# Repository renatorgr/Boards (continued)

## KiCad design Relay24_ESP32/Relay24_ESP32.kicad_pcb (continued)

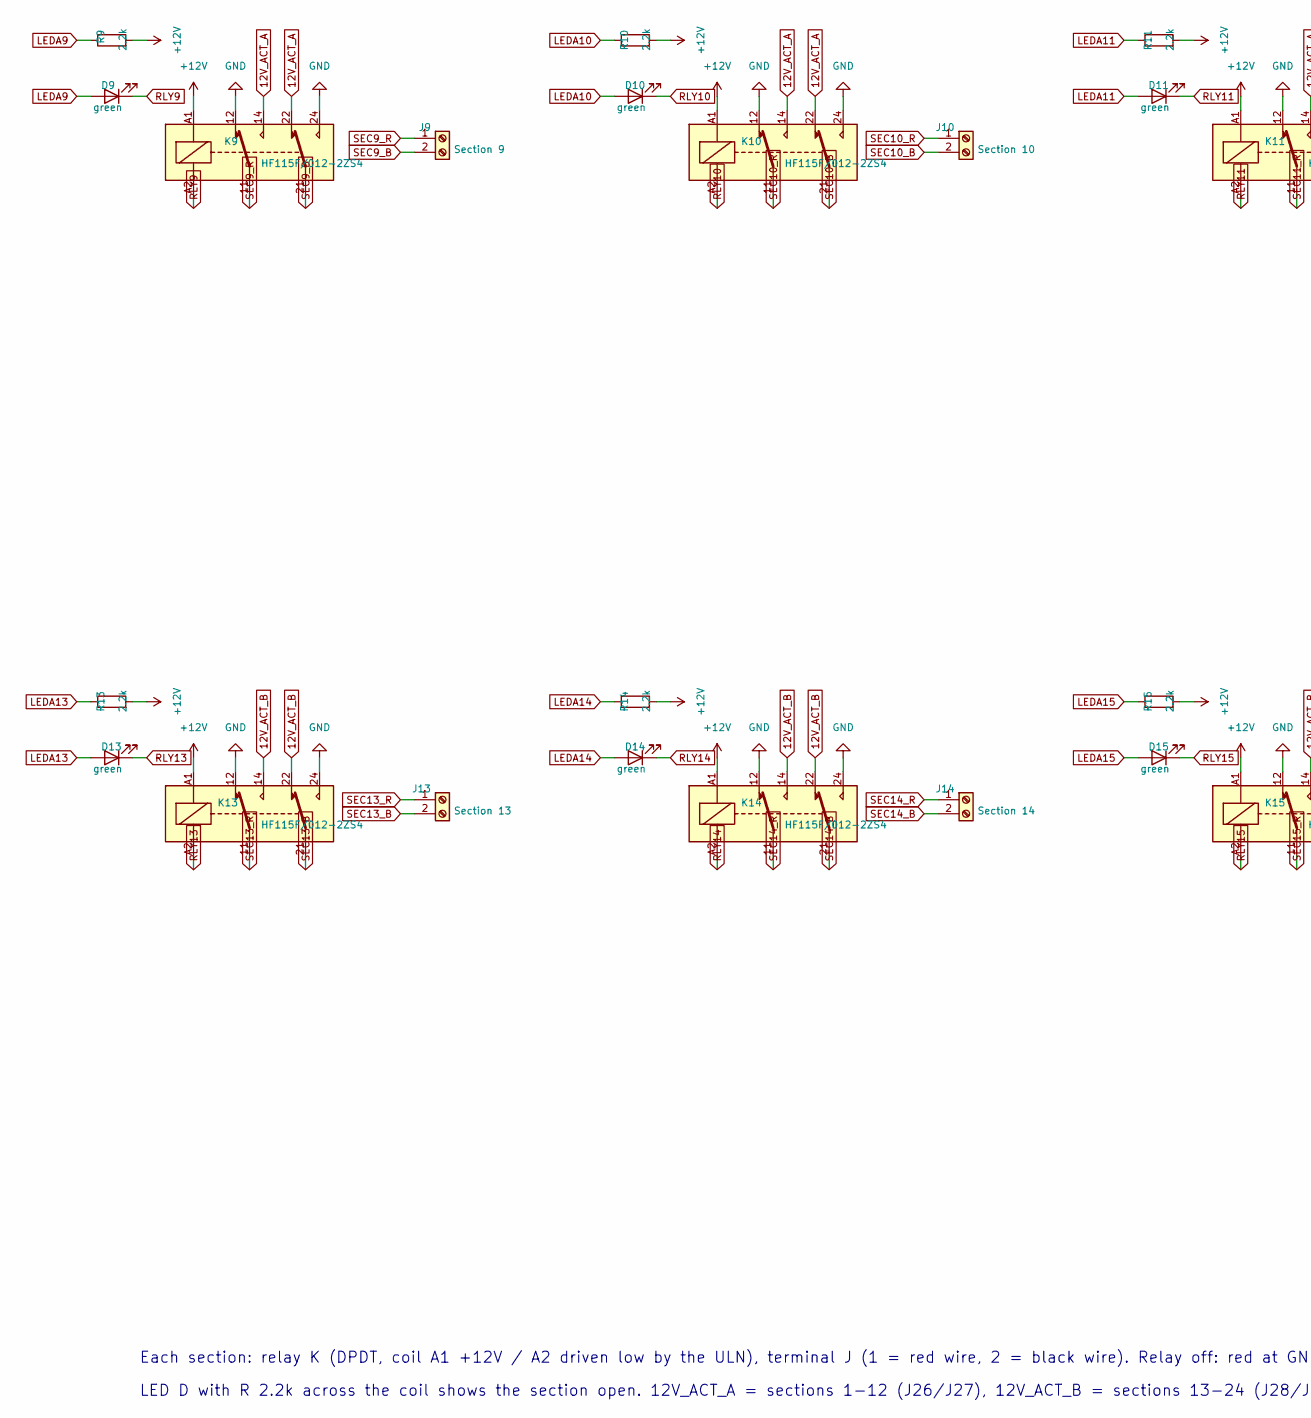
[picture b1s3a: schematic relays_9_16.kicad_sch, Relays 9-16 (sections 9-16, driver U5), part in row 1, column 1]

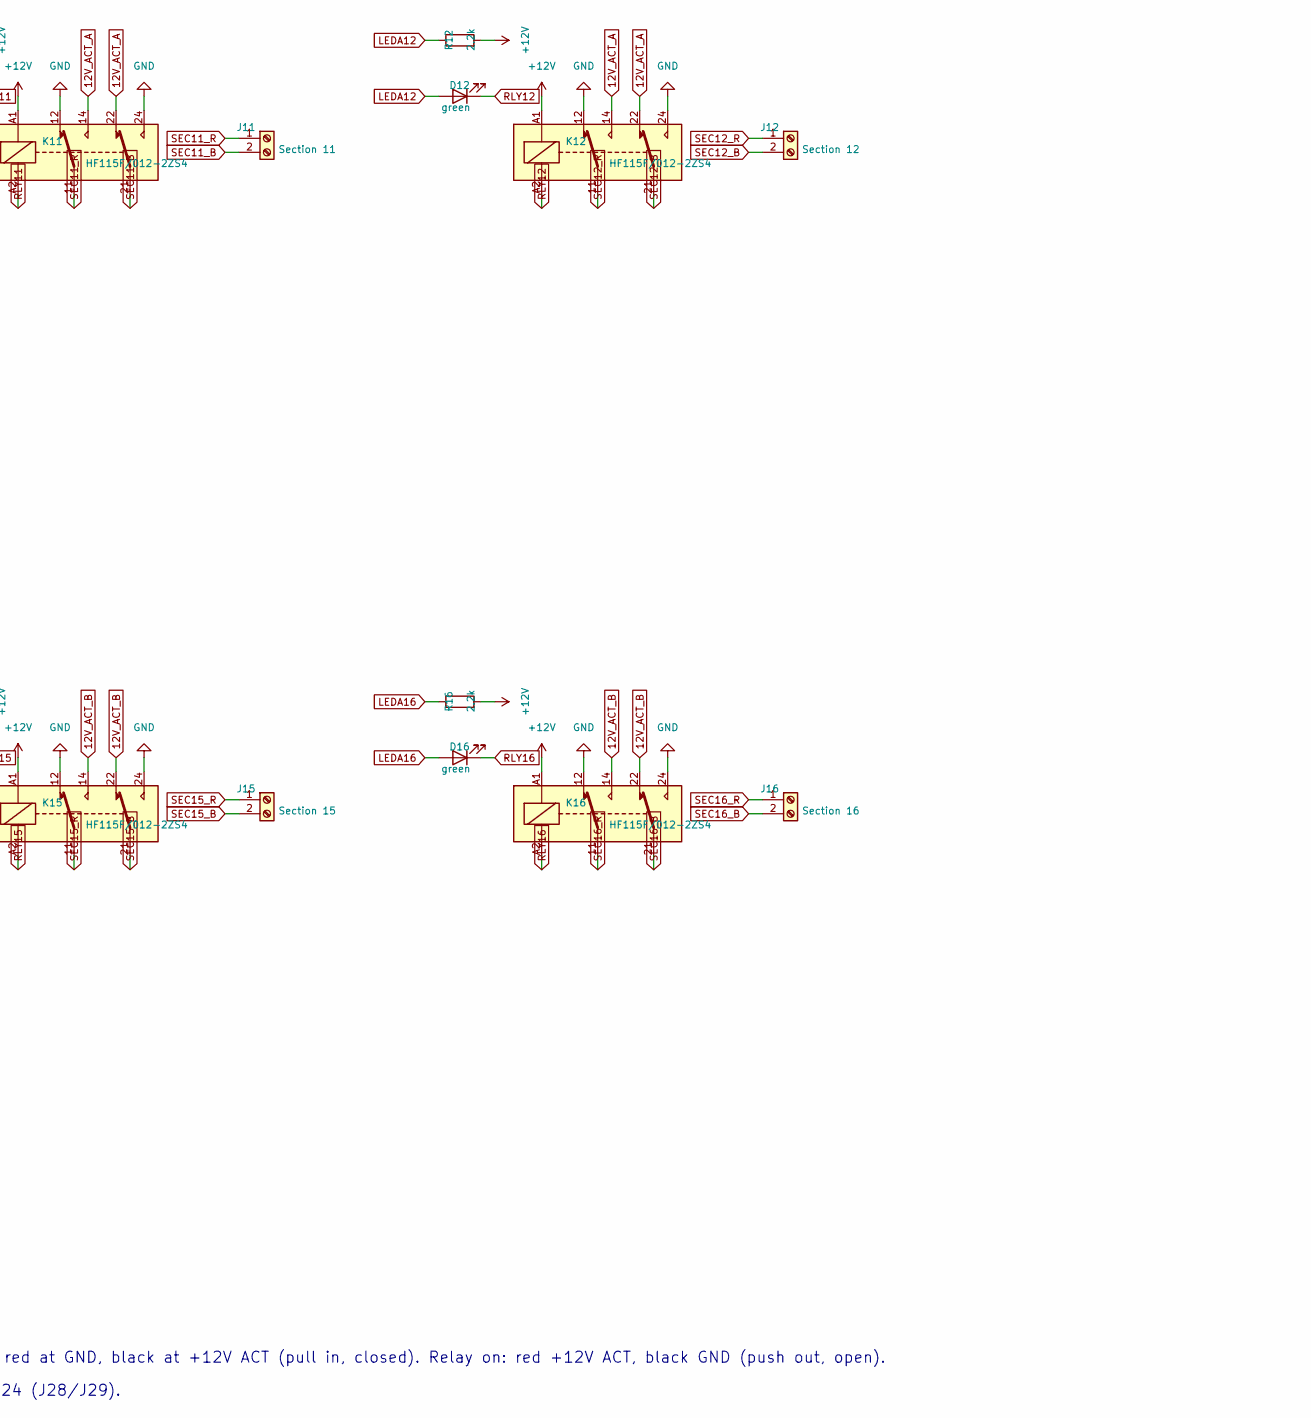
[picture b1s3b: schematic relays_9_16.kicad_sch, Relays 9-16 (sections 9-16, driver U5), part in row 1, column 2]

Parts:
D9, D10, D11, D12, D13, D14, D15, D16: green; LED_0603_1608Metric; LCSC C965805
J9: Section 9; TerminalBlock_bornier-2_P5.08mm; LCSC C8465
J10: Section 10; TerminalBlock_bornier-2_P5.08mm; LCSC C8465
J11: Section 11; TerminalBlock_bornier-2_P5.08mm; LCSC C8465
J12: Section 12; TerminalBlock_bornier-2_P5.08mm; LCSC C8465
J13: Section 13; TerminalBlock_bornier-2_P5.08mm; LCSC C8465
J14: Section 14; TerminalBlock_bornier-2_P5.08mm; LCSC C8465
J15: Section 15; TerminalBlock_bornier-2_P5.08mm; LCSC C8465
J16: Section 16; TerminalBlock_bornier-2_P5.08mm; LCSC C8465
K9, K10, K11, K12, K13, K14, K15, K16: HF115F/012-2ZS4; Relay_DPDT_Omron_G2RL-2; LCSC C163534
R9, R10, R11, R12, R13, R14, R15, R16: 2.2k; R_0603_1608Metric; LCSC C4190

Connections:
12V_ACT_A: K9.14, K9.22, K10.14, K10.22, K11.14, K11.22, K12.14, K12.22; also elsewhere on the board
12V_ACT_B: K13.14, K13.22, K14.14, K14.22, K15.14, K15.22, K16.14, K16.22; also elsewhere on the board
+12V: K9.A1, K10.A1, K11.A1, K12.A1, K13.A1, K14.A1, K15.A1, K16.A1, R9.2, R10.2, R11.2, R12.2, R13.2, R14.2, R15.2, R16.2; also elsewhere on the board
GND: K9.12, K9.24, K10.12, K10.24, K11.12, K11.24, K12.12, K12.24, K13.12, K13.24, K14.12, K14.24, K15.12, K15.24, K16.12, K16.24; also elsewhere on the board
LEDA9: D9.2 (A), R9.1
LEDA10: D10.2 (A), R10.1
LEDA11: D11.2 (A), R11.1
LEDA12: D12.2 (A), R12.1
LEDA13: D13.2 (A), R13.1
LEDA14: D14.2 (A), R14.1
LEDA15: D15.2 (A), R15.1
LEDA16: D16.2 (A), R16.1
RLY9: D9.1 (K), K9.A2; also elsewhere on the board
RLY10: D10.1 (K), K10.A2; also elsewhere on the board
RLY11: D11.1 (K), K11.A2; also elsewhere on the board
RLY12: D12.1 (K), K12.A2; also elsewhere on the board
RLY13: D13.1 (K), K13.A2; also elsewhere on the board
RLY14: D14.1 (K), K14.A2; also elsewhere on the board
RLY15: D15.1 (K), K15.A2; also elsewhere on the board
RLY16: D16.1 (K), K16.A2; also elsewhere on the board
SEC9_B: J9.2, K9.21
SEC9_R: J9.1, K9.11
SEC10_B: J10.2, K10.21
SEC10_R: J10.1, K10.11
SEC11_B: J11.2, K11.21
SEC11_R: J11.1, K11.11
SEC12_B: J12.2, K12.21
SEC12_R: J12.1, K12.11
SEC13_B: J13.2, K13.21
SEC13_R: J13.1, K13.11
SEC14_B: J14.2, K14.21
SEC14_R: J14.1, K14.11
SEC15_B: J15.2, K15.21
SEC15_R: J15.1, K15.11
SEC16_B: J16.2, K16.21
SEC16_R: J16.1, K16.11

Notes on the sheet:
Each section: relay K (DPDT, coil A1 +12V / A2 driven low by the ULN), terminal J (1 = red wire, 2 = black wire). Relay off: red at GND, black at +12V ACT (pull in, closed). Relay on: red +12V ACT, black GND (push out, open).
LED D with R 2.2k across the coil shows the section open. 12V_ACT_A = sections 1-12 (J26/J27), 12V_ACT_B = sections 13-24 (J28/J29).

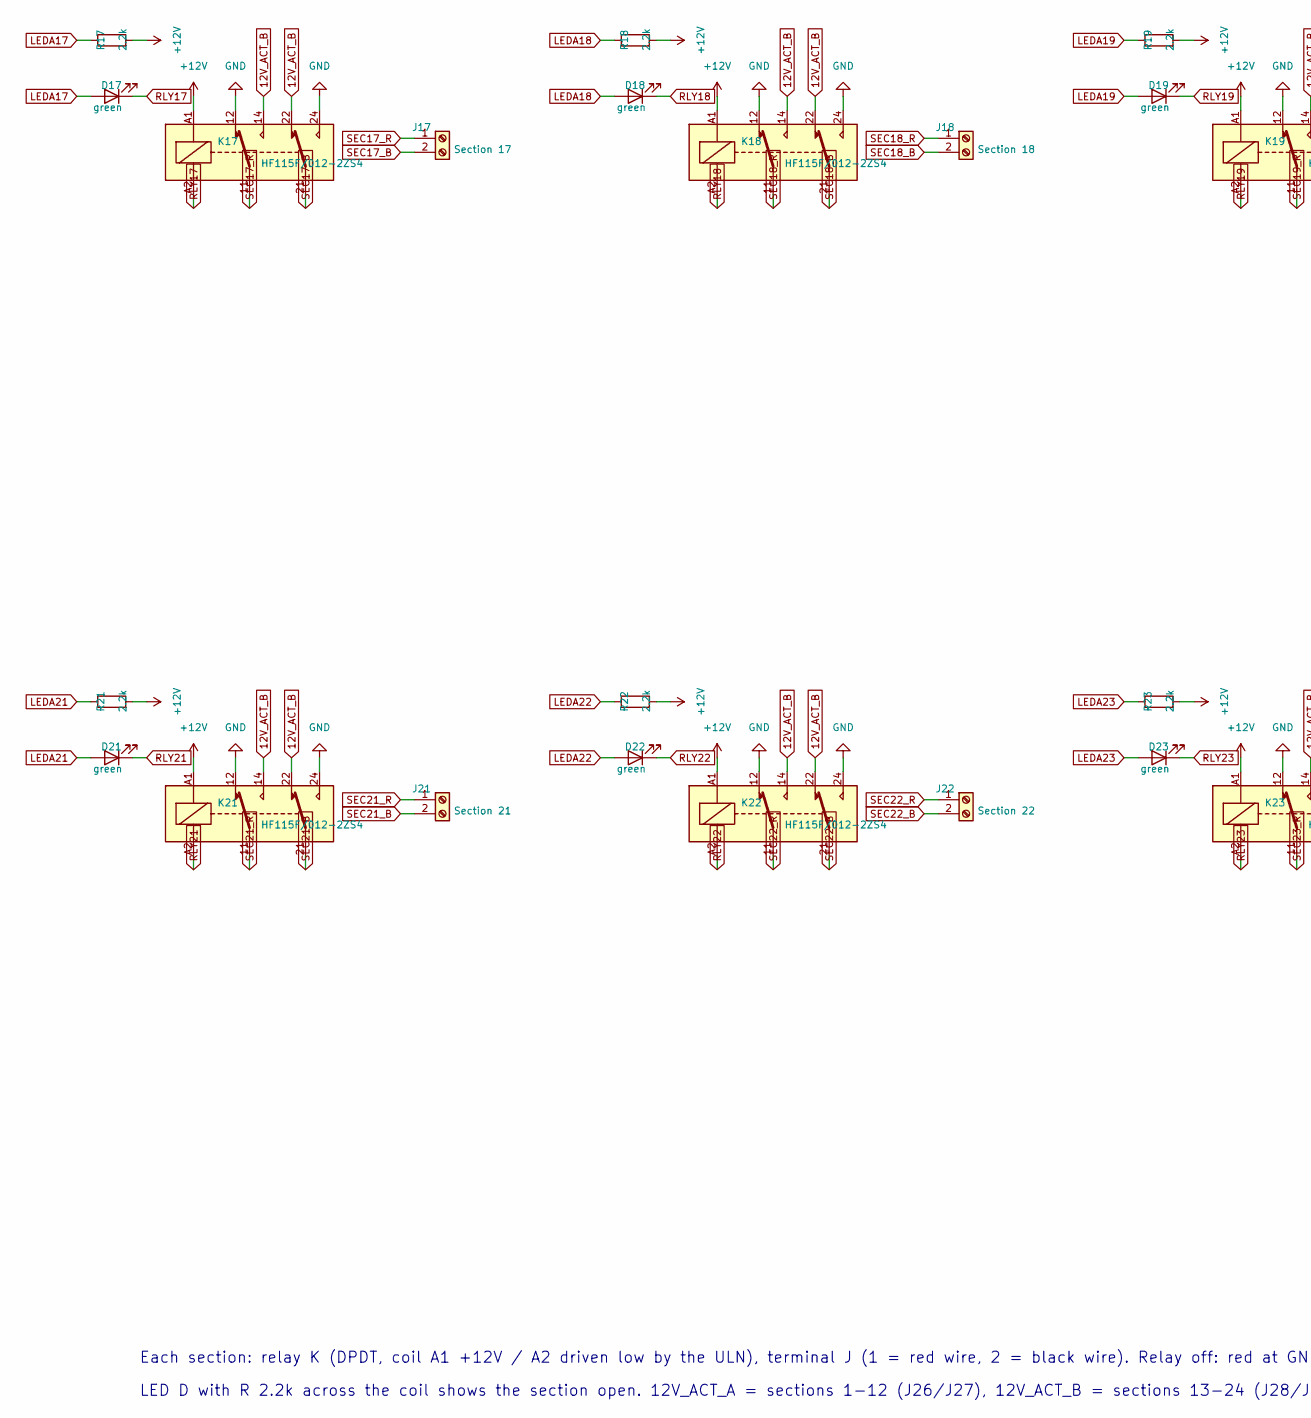
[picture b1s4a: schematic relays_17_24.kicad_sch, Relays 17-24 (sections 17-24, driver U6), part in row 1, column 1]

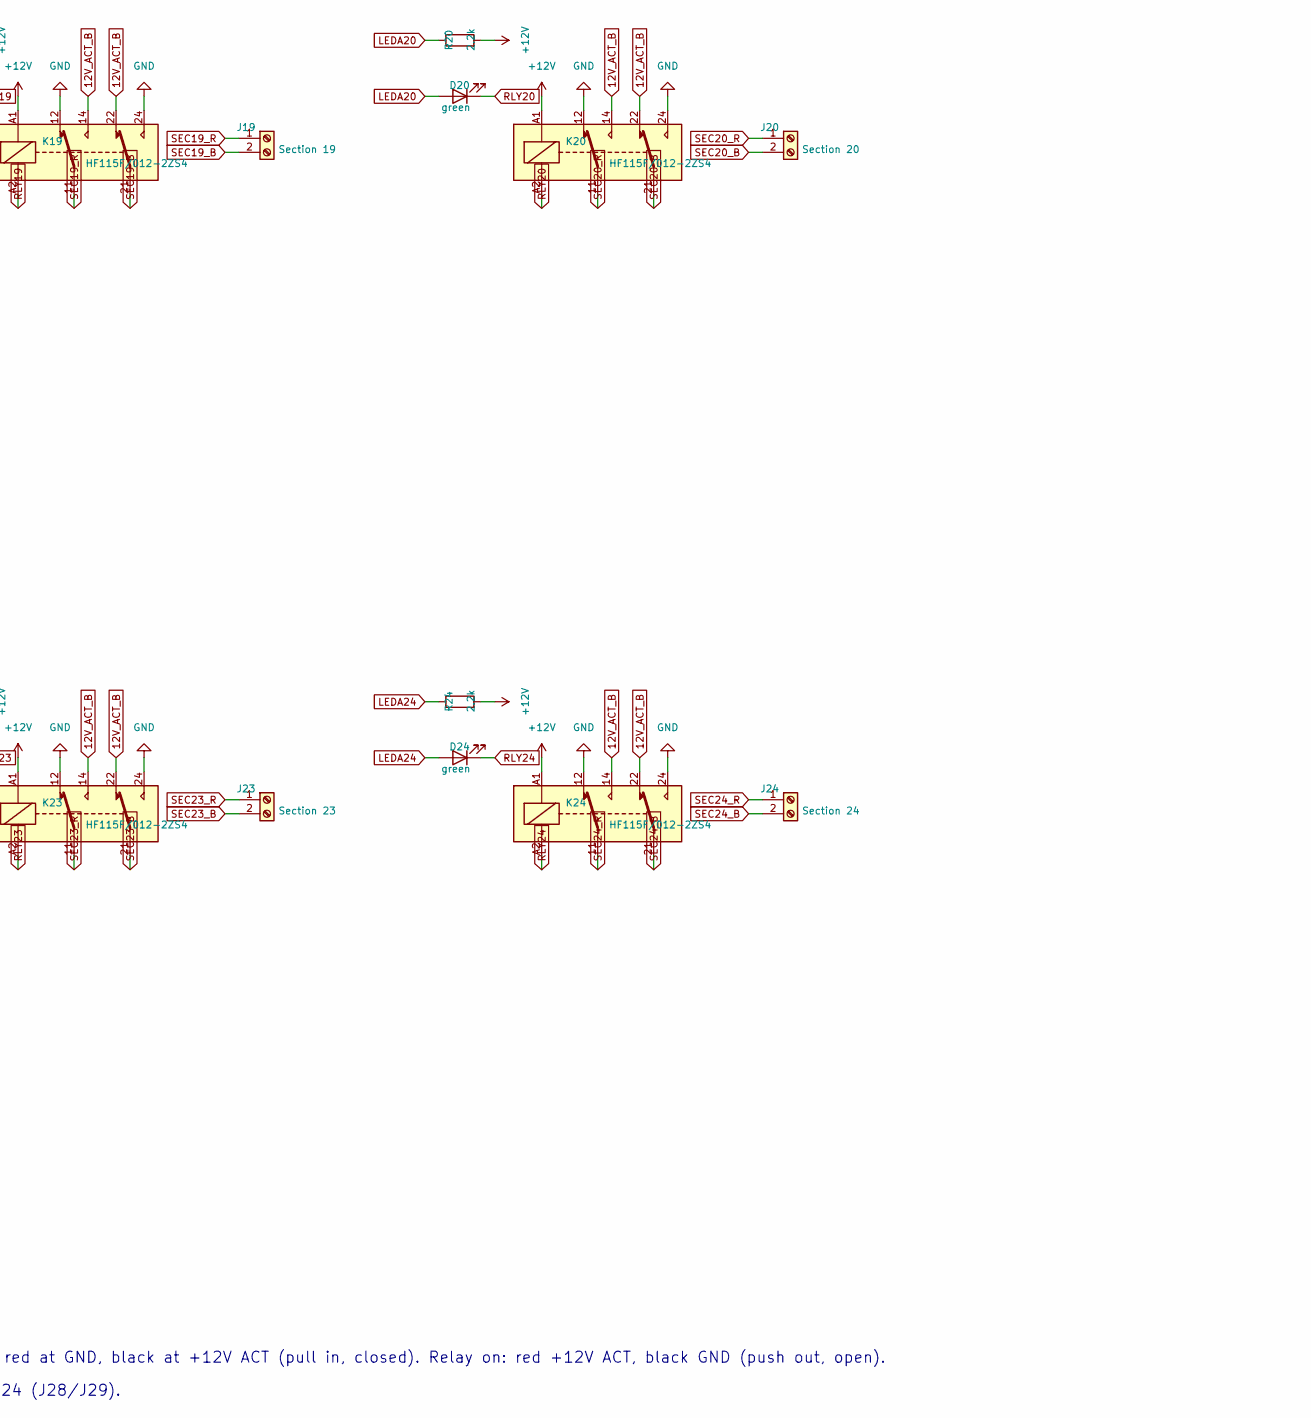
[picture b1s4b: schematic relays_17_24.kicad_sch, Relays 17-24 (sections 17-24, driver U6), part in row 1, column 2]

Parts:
D17, D18, D19, D20, D21, D22, D23, D24: green; LED_0603_1608Metric; LCSC C965805
J17: Section 17; TerminalBlock_bornier-2_P5.08mm; LCSC C8465
J18: Section 18; TerminalBlock_bornier-2_P5.08mm; LCSC C8465
J19: Section 19; TerminalBlock_bornier-2_P5.08mm; LCSC C8465
J20: Section 20; TerminalBlock_bornier-2_P5.08mm; LCSC C8465
J21: Section 21; TerminalBlock_bornier-2_P5.08mm; LCSC C8465
J22: Section 22; TerminalBlock_bornier-2_P5.08mm; LCSC C8465
J23: Section 23; TerminalBlock_bornier-2_P5.08mm; LCSC C8465
J24: Section 24; TerminalBlock_bornier-2_P5.08mm; LCSC C8465
K17, K18, K19, K20, K21, K22, K23, K24: HF115F/012-2ZS4; Relay_DPDT_Omron_G2RL-2; LCSC C163534
R17, R18, R19, R20, R21, R22, R23, R24: 2.2k; R_0603_1608Metric; LCSC C4190

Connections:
12V_ACT_B: K17.14, K17.22, K18.14, K18.22, K19.14, K19.22, K20.14, K20.22, K21.14, K21.22, K22.14, K22.22, K23.14, K23.22, K24.14, K24.22; also elsewhere on the board
+12V: K17.A1, K18.A1, K19.A1, K20.A1, K21.A1, K22.A1, K23.A1, K24.A1, R17.2, R18.2, R19.2, R20.2, R21.2, R22.2, R23.2, R24.2; also elsewhere on the board
GND: K17.12, K17.24, K18.12, K18.24, K19.12, K19.24, K20.12, K20.24, K21.12, K21.24, K22.12, K22.24, K23.12, K23.24, K24.12, K24.24; also elsewhere on the board
LEDA17: D17.2 (A), R17.1
LEDA18: D18.2 (A), R18.1
LEDA19: D19.2 (A), R19.1
LEDA20: D20.2 (A), R20.1
LEDA21: D21.2 (A), R21.1
LEDA22: D22.2 (A), R22.1
LEDA23: D23.2 (A), R23.1
LEDA24: D24.2 (A), R24.1
RLY17: D17.1 (K), K17.A2; also elsewhere on the board
RLY18: D18.1 (K), K18.A2; also elsewhere on the board
RLY19: D19.1 (K), K19.A2; also elsewhere on the board
RLY20: D20.1 (K), K20.A2; also elsewhere on the board
RLY21: D21.1 (K), K21.A2; also elsewhere on the board
RLY22: D22.1 (K), K22.A2; also elsewhere on the board
RLY23: D23.1 (K), K23.A2; also elsewhere on the board
RLY24: D24.1 (K), K24.A2; also elsewhere on the board
SEC17_B: J17.2, K17.21
SEC17_R: J17.1, K17.11
SEC18_B: J18.2, K18.21
SEC18_R: J18.1, K18.11
SEC19_B: J19.2, K19.21
SEC19_R: J19.1, K19.11
SEC20_B: J20.2, K20.21
SEC20_R: J20.1, K20.11
SEC21_B: J21.2, K21.21
SEC21_R: J21.1, K21.11
SEC22_B: J22.2, K22.21
SEC22_R: J22.1, K22.11
SEC23_B: J23.2, K23.21
SEC23_R: J23.1, K23.11
SEC24_B: J24.2, K24.21
SEC24_R: J24.1, K24.11

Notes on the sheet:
Each section: relay K (DPDT, coil A1 +12V / A2 driven low by the ULN), terminal J (1 = red wire, 2 = black wire). Relay off: red at GND, black at +12V ACT (pull in, closed). Relay on: red +12V ACT, black GND (push out, open).
LED D with R 2.2k across the coil shows the section open. 12V_ACT_A = sections 1-12 (J26/J27), 12V_ACT_B = sections 13-24 (J28/J29).

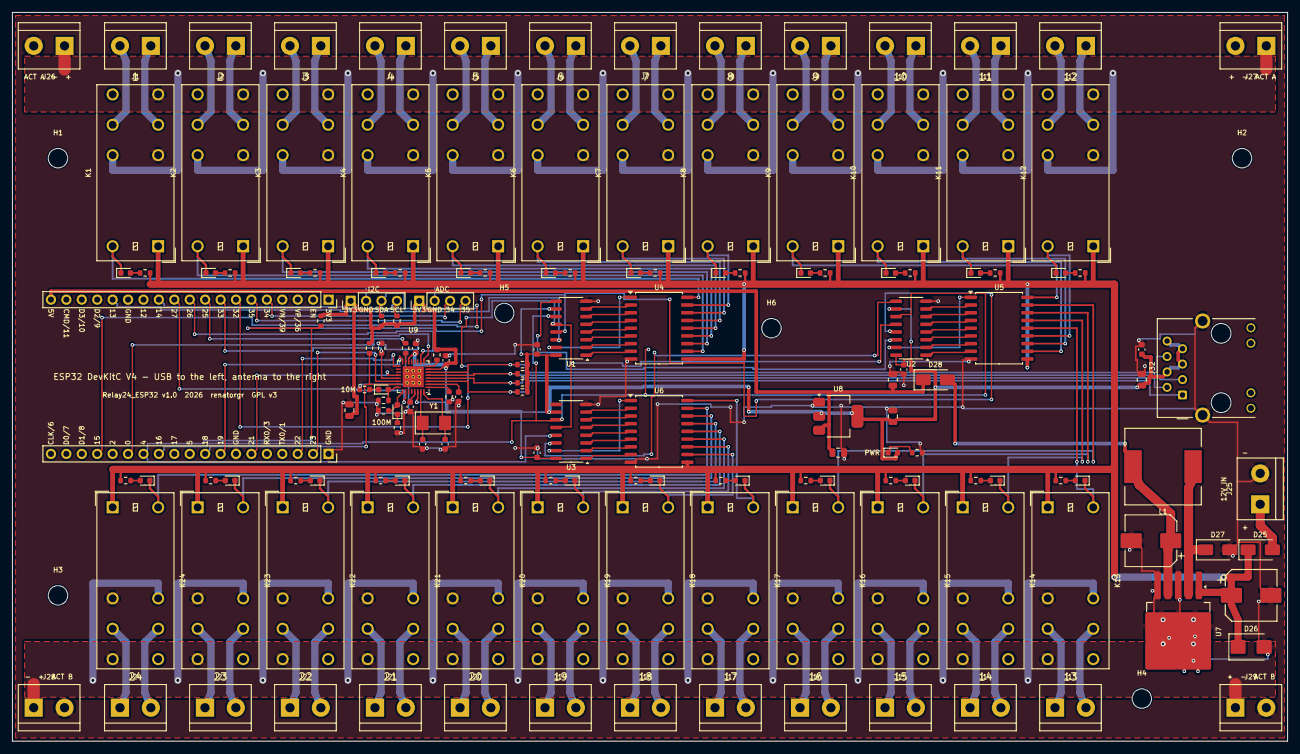
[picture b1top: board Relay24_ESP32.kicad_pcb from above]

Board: 2 copper layers, 210.0 x 120.0 mm, 164 parts (0 on the bottom side), 165 nets.

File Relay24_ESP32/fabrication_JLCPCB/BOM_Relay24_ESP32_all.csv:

Comment,Designator,Footprint,LCSC Part #
100nF,"C1,C2,C3,C30,C31,C32,C33,C36",C_0603_1608Metric,C14663
100uF 50V,C25,CP_Elec_8x10,C97812
220uF 25V,C26,CP_Elec_8x10,C165536
10uF,"C27,C28,C29,C37,C38",C_0805_2012Metric,C15850
33pF,"C34,C35",C_0603_1608Metric,C1663
green,"D1,D2,D3,D4,D5,D6,D7,D8,D9,D10,D11,D12,D13,D14,D15,D16,D17,D18,D19,D20,D21,D22,D23,D24,D31",LED_0603_1608Metric,C965805
SS54,"D25,D27",D_SMA,C22452
SMBJ18A,D26,D_SMB,C151256
SS34,D28,D_SMA,C8678
red,D29,LED_0603_1608Metric,C2286
yellow,D30,LED_0603_1608Metric,C965802
Section 1,J1,TerminalBlock_bornier-2_P5.08mm,C8465
Section 2,J2,TerminalBlock_bornier-2_P5.08mm,C8465
Section 3,J3,TerminalBlock_bornier-2_P5.08mm,C8465
Section 4,J4,TerminalBlock_bornier-2_P5.08mm,C8465
Section 5,J5,TerminalBlock_bornier-2_P5.08mm,C8465
Section 6,J6,TerminalBlock_bornier-2_P5.08mm,C8465
Section 7,J7,TerminalBlock_bornier-2_P5.08mm,C8465
Section 8,J8,TerminalBlock_bornier-2_P5.08mm,C8465
Section 9,J9,TerminalBlock_bornier-2_P5.08mm,C8465
Section 10,J10,TerminalBlock_bornier-2_P5.08mm,C8465
Section 11,J11,TerminalBlock_bornier-2_P5.08mm,C8465
Section 12,J12,TerminalBlock_bornier-2_P5.08mm,C8465
Section 13,J13,TerminalBlock_bornier-2_P5.08mm,C8465
Section 14,J14,TerminalBlock_bornier-2_P5.08mm,C8465
Section 15,J15,TerminalBlock_bornier-2_P5.08mm,C8465
Section 16,J16,TerminalBlock_bornier-2_P5.08mm,C8465
Section 17,J17,TerminalBlock_bornier-2_P5.08mm,C8465
Section 18,J18,TerminalBlock_bornier-2_P5.08mm,C8465
Section 19,J19,TerminalBlock_bornier-2_P5.08mm,C8465
Section 20,J20,TerminalBlock_bornier-2_P5.08mm,C8465
Section 21,J21,TerminalBlock_bornier-2_P5.08mm,C8465
Section 22,J22,TerminalBlock_bornier-2_P5.08mm,C8465
Section 23,J23,TerminalBlock_bornier-2_P5.08mm,C8465
Section 24,J24,TerminalBlock_bornier-2_P5.08mm,C8465
12V IN,J25,TerminalBlock_bornier-2_P5.08mm,C8465
12V ACT A (left),J26,TerminalBlock_bornier-2_P5.08mm,C8465
12V ACT A (right),J27,TerminalBlock_bornier-2_P5.08mm,C8465
12V ACT B (left),J28,TerminalBlock_bornier-2_P5.08mm,C8465
12V ACT B (right),J29,TerminalBlock_bornier-2_P5.08mm,C8465
DevKitC J2 (3V3..5V),J30,PinSocket_1x19_P2.54mm_Vertical,C319202
DevKitC J3 (GND..CLK),J31,PinSocket_1x19_P2.54mm_Vertical,C319202
HR911105A,J32,RJ45_Hanrun_HR911105A_Horizontal,C12074
I2C,J33,PinHeader_1x04_P2.54mm_Vertical,C124378
Analog,J34,PinHeader_1x04_P2.54mm_Vertical,C124378
HF115F/012-2ZS4,"K1,K2,K3,K4,K5,K6,K7,K8,K9,K10,K11,K12,K13,K14,K15,K16,K17,K18,K19,K20,K21,K22,K23,K24",Relay_DPDT_Omron_G2RL-2,C163534
33uH 3A,L1,L_12x12mm_H8mm,C2929502
2.2k,"R1,R2,R3,R4,R5,R6,R7,R8,R9,R10,R11,R12,R13,R14,R15,R16,R17,R18,R19,R20,R21,R22,R23,R24",R_0603_1608Metric,C4190
1k,R29,R_0603_1608Metric,C21190
33,R30,R_0603_1608Metric,C23140
2.49k 1%,R31,R_0603_1608Metric,C136931
4.7k,"R32,R35,R36,R44,R45,R46",R_0603_1608Metric,C23162
10k,R33,R_0603_1608Metric,C25804
1.5k,R34,R_0603_1608Metric,C22843
49.9 1%,"R38,R39,R40,R41",R_0603_1608Metric,C23185
330,"R42,R43",R_0603_1608Metric,C23138
74HC595,"U1,U2,U3",SOIC-16_3.9x9.9mm_P1.27mm,C5947
ULN2803A,"U4,U5,U6",SOIC-18W_7.5x11.6mm_P1.27mm,C22437476
LM2596S-5.0,U7,TO-263-5_TabPin3,C347421
AMS1117-3.3,U8,SOT-223-3_TabPin2,C6186
RTL8201F,U9,QFN-32-1EP_5x5mm_P0.5mm_EP3.45x3.45mm_ThermalVias,C45044
25MHz,Y1,Crystal_SMD_5032-2Pin_5.0x3.2mm,C112569

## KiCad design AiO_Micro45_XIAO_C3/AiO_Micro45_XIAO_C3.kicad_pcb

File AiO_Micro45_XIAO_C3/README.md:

# XIAO ESP32C3 adapter for the AiO v4.5 Micro (GPS2 socket → Serial2)

A small board (27.3 × 24.4 mm, 2 layers) that plugs into the **second GPS socket ("Dual-Left", U11)** of the AiO v4.5 Micro, in place of a simpleRTK2B Micro, and connects a **Seeed XIAO ESP32C3** (or **ESP32S3**) to the **Teensy's Serial2** (pins 7 and 8). The XIAO plugs into two female headers on the adapter.

## Connections

| Socket pin | On the AiO v4.5 Micro | On the adapter |
|---|---|---|
| 1 | 3.3 V (1 A K7803M regulator) | C1 22 µF, then U2 (LM66100 ideal diode) → XIAO 3V3 + C2 22 µF |
| 2 | Teensy pin 7 (RX2) | R1 1 kΩ → D6 (TX, GPIO21) |
| 3 | Teensy pin 8 (TX2) | R2 1 kΩ → D7 (RX, GPIO20) |
| 10, 11 | GND | GND |
| 6, 7, 8 | F9P micro-USB | not connected |
| 16 | pin 12 of the GPS1 socket (dual F9P only) | not connected |
| 18 | LED RTK_STAT_1 | not connected |
| others | — | not connected |

The plug is two 1x10 male headers: J1 = socket pins 1–10, J2 = socket pins 11–20 (J2 pin 1 = socket pin 11). The XIAO plugs into two 1x7 female headers: J3 = XIAO pins 1–7 (D0–D6), J4 = XIAO pins 8–14 (D7–5V).

The positions of the 20 pins were copied from the official AiO v4.5 Micro PCB file (EasyEDA, 2024-02-05) and checked against the schematic: 0.00 mm difference. The outline stays inside the drawing of the original module on the Micro's silkscreen, with the same cut corner (on the side of LED1 and the RJ45 jack).

## Why the ideal diode (U2)

- On the Micro the GPS2 socket only has 3.3 V, so the XIAO is fed through its 3V3 pin. An ordinary diode would drop it to about 3.0 V, too low for the ESP32 WiFi.
- U2 (TI LM66100) is an "ideal diode": current flows only from the AiO to the XIAO, with a drop of a few tens of mV. Its CE pin is tied to its output, which turns it off as soon as the XIAO side is higher than the AiO side.
- So the XIAO's USB-C can now be plugged in with the adapter on the board: the XIAO powers itself from USB and U2 stops that power from going back into the AiO's 3.3 V (GPS1 F9P, LEDs, radio, K7803M).
- R1 and R2 are 1 kΩ (100 Ω in v1.1). If the XIAO is on USB with the AiO switched off, its TX pin feeds the unpowered Teensy through R1; 1 kΩ keeps that current to about 3 mA. At 460800 baud, 1 kΩ makes no difference.

## Files

- `AiO_Micro45_XIAO_C3.kicad_pro / .kicad_sch / .kicad_pcb`: KiCad 7 project (schematic + PCB), with its own libraries (`AiO_XIAO_Adapter.pretty`, `AiO_XIAO_Adapter.kicad_sym`).
- `fabrication_JLCPCB/Gerber_AiO_Micro45_XIAO_C3.zip`: Gerbers + drill file, ready for JLCPCB.
- `fabrication_JLCPCB/BOM_…csv` and `CPL_…csv`: for JLCPCB's assembly (R1, R2, C1, C2, U2 and the XIAO sockets J3, J4 on the top side, the two pin headers J1 and J2 on the bottom side).
- `fabrication_JLCPCB/BOM_…_top_only.csv` and `CPL_…_top_only.csv`: the same without J1 and J2, for an assembly on the top side only.
- In this folder: the schematic as a PDF (`adapter_schematic.pdf`), views of the board (`adapter_PCB.png`) and its position on the Micro (`GPS2_socket_view.png`).

## Opening it in EasyEDA

EasyEDA Pro: **File → Import → KiCad**, then choose the project folder (or the .zip). It imports the schematic and the PCB.
EasyEDA is not needed to order the board: the Gerber zip goes straight to JLCPCB.

## Ordering (JLCPCB)

- Gerber: `Gerber_AiO_Micro45_XIAO_C3.zip`. 2 layers, 1.6 mm, any colour. The default settings are fine (minimum track 0.25 mm, minimum hole 0.3 mm).
- Assembly: BOM + CPL. JLCPCB solders everything except the XIAO:
  - R1, R2, C1, C2 and U2: SMD parts on the top side;
  - the pin headers J1 and J2: through-hole parts on the **bottom** side, with the long pins pointing down (away from the board). The CPL already gives them on the bottom layer, at the centre of each header;
  - the two female headers J3 and J4 for the XIAO: through-hole parts on the **top** side.
- Through-hole assembly costs a little more than SMD only.
- There are parts on both sides, so choose **Standard PCBA** with assembly on **both sides**. With Economic PCBA or top side only, JLCPCB leaves out J1 and J2 (they are on the bottom) and stops with "Coordinate file missing data for: J1, J2".
- Cheaper alternative: Economic PCBA, top side only, with `BOM_…_top_only.csv` and `CPL_…_top_only.csv` (the same files without J1 and J2), and solder J1 and J2 by hand.
- In JLCPCB's placement preview, check that J1 and J2 are on the bottom side, over the two rows of 10 holes, and J3 and J4 on the top side, over the two rows of 7 holes.
- Also check U2's pin 1 in the preview: pin 1 (VIN, marked with a small triangle on the silkscreen) must be at the corner of U2 nearest to the J4 row and the USB-C side. Chip rotations in the CPL are sometimes off by 90° or 180° at JLCPCB; if the dot of the chip is elsewhere, rotate it in the preview.

| Ref. | Part | LCSC |
|---|---|---|
| R1, R2 | 1 kΩ 1 % 0805 | C17513 |
| C1, C2 | 22 µF 0805 X5R | C45783 |
| U2 | TI LM66100DCKR ideal diode, SC-70-6 | C2869734 (or C2832141, LM66100DCKT) |
| J1, J2 | 1x10 male header, **2.00 mm pitch**, HCTL PZ200-1-10-Z | C2905956 |
| J3, J4 | 1x07 female header, 2.54 mm, 8.5 mm high, HCTL PM254-1-07-Z-8.5 | C2897370 |
| U1 | Seeed XIAO ESP32C3 or ESP32S3, plugged into J3 / J4 | (not assembled) |

The 2.00 mm headers have 4 mm mating pins and a 2 mm insulator.

## Assembly

1. Only if the board did not come assembled: U2, R1, R2, C1 and C2, then the headers. U2 is very small (SC-70-6): pin 1 goes at the triangle mark.
2. **The 2.00 mm male headers go underneath**, with the pins pointing down. When soldering them by hand, to get them well aligned: push them into the Micro's GPS2 socket, lay the adapter on top and solder them from above.
3. **XIAO:** solder the two 1x7 male headers that come with it **underneath the XIAO**, long pins pointing down. To keep them straight, push them into J3 and J4 first, lay the XIAO on top and solder from above.
4. **Plug the XIAO into J3 and J4 with its USB-C at the "USB-C" mark.** The two rows have 7 pins each, so the XIAO also goes in turned 180°: that way the 3.3 V goes into D4 instead of 3V3 and the XIAO can be damaged. Check the USB-C mark before powering the AiO.
5. Under J3 (the D0–D6 row), on the Micro, there is resistor R31: check that the solder joints of J3 underneath the adapter do not touch it.
6. Orientation on the Micro: the cut corner of the adapter matches the cut corner drawn on the silkscreen of the GPS2 socket, and pin 1 (square pad, dot on the silkscreen) sits next to pin 1 of the socket.

## Cautions

- The XIAO is powered through its 3V3 pin, from the board's 3.3 V through U2. From v1.2 the XIAO's USB-C can be plugged in with the adapter on the Micro (on v1.1 boards it must not be: unplug the XIAO to program it by USB, or use WiFi OTA).
- The USB-C plug goes in from the right edge of the adapter (towards LED3 and the mini-USB connector of the Micro): check that the cable fits in your box.
- On the sockets the XIAO sits about 11 mm higher than soldered flat (8.5 mm socket + 2.5 mm of the male header). Check that the box lid closes.
- Tractor vibration: hold the XIAO in its sockets, for example with a cable tie around the XIAO and the adapter, or a dot of neutral-cure silicone at the corners (not on the U.FL connector or the buttons).
- Hammond 1455 boxes are aluminium: use an external WiFi antenna on the XIAO's U.FL connector, taken out through the lid.
- With the adapter in place the GPS2 socket cannot hold a second F9P (dual F9P).

## Firmware

- Teensy: firmware `v4.5_AiO_WEB`, Serial2 (pins 7 RX2 and 8 TX2) at **460800**. On its web page, Settings → "GPS2 port" must be on automatic (the default): the Teensy finds the XIAO by its hello.
- XIAO: the program `v4.5_XIAO_ESP32` that comes in the firmware zip (already compiled in `v4.5_XIAO_ESP32_bin`). It uses UART1 on D7 (RX, GPIO20) and D6 (TX, GPIO21) at 460800 and empties the receive FIFO at 64 bytes (`setRxFIFOFull(64)`).
- The XIAO ESP32S3 fits too: same size and pins (D6 = GPIO43 TX, D7 = GPIO44 RX).
- When it starts, the ESP32-C3 writes a few boot lines at 115200 on GPIO21: the Teensy receives garbage for half a second, and the firmware ignores it.
- The official firmware v26 (Firmware_Teensy_AiO-New-Dawn) uses this same link (Serial2) for its ESP32, also at 460800. See `docs/ESP32_BRIDGE_INTERFACE.md` in that repository.

## Checks done

- The schematic and the PCB have the same connections (netlist exported from the schematic = PCB connections).
- KiCad 7 DRC: 0 errors, 0 unconnected items (v1.2).
- Pins and connections checked against the official AiO v4.5 Micro schematic and PCB (AgOpenGPS-Official/Boards).
- The XIAO sockets J3 and J4 are on the XIAO pin positions of Seeed's official KiCad library (XIAO-ESP32-C3-DIP-SMD): 2 × 7 pins, 2.54 mm, rows 15.24 mm apart.
- J1 and J2 are on the bottom side and J3, J4 on the top side, in the PCB and in the CPL; the drill file has the same 44 holes as version 1.0, plus 2 vias for U2 in v1.2.
- U2 pins used: 1 VIN, 2 GND, 3 CE, 6 VOUT (pins 4 and 5 are left unconnected). Check against the TI datasheet before the first order.
- Not yet made or tested on a real board.

## Versions

- **1.2** (20 Oct 2026): U2 (LM66100 ideal diode) between the AiO 3.3 V and the XIAO 3V3 pin, with C2 22 µF on the XIAO side, so the XIAO's USB-C can be used with the adapter on the board. R1 and R2 changed from 100 Ω to 1 kΩ. Same outline, same header holes, same XIAO position.
- **1.1** (19 Oct 2026): the plug is now two 1x10 2.00 mm headers (J1, J2) with LCSC codes in the BOM and the CPL (bottom side), so JLCPCB solders them too. The XIAO plugs into two 1x7 female headers (J3, J4, top side, also soldered by JLCPCB) instead of being soldered to the board. Same holes and tracks as 1.0.
- **1.0** (14 Oct 2026): first version.

## Credits

- Design: renatorgr, with Claude (Anthropic), 2026.
- Pin positions: official AiO v4.5 Micro board files (EasyEDA PCB 2024-02-05 and schematic), AgOpenGPS-Official/Boards.
- XIAO pin positions: Seeed Studio OPL KiCad library (XIAO-ESP32-C3-DIP-SMD). 0805 and SOT-363 (SC-70-6) footprints: KiCad standard library.

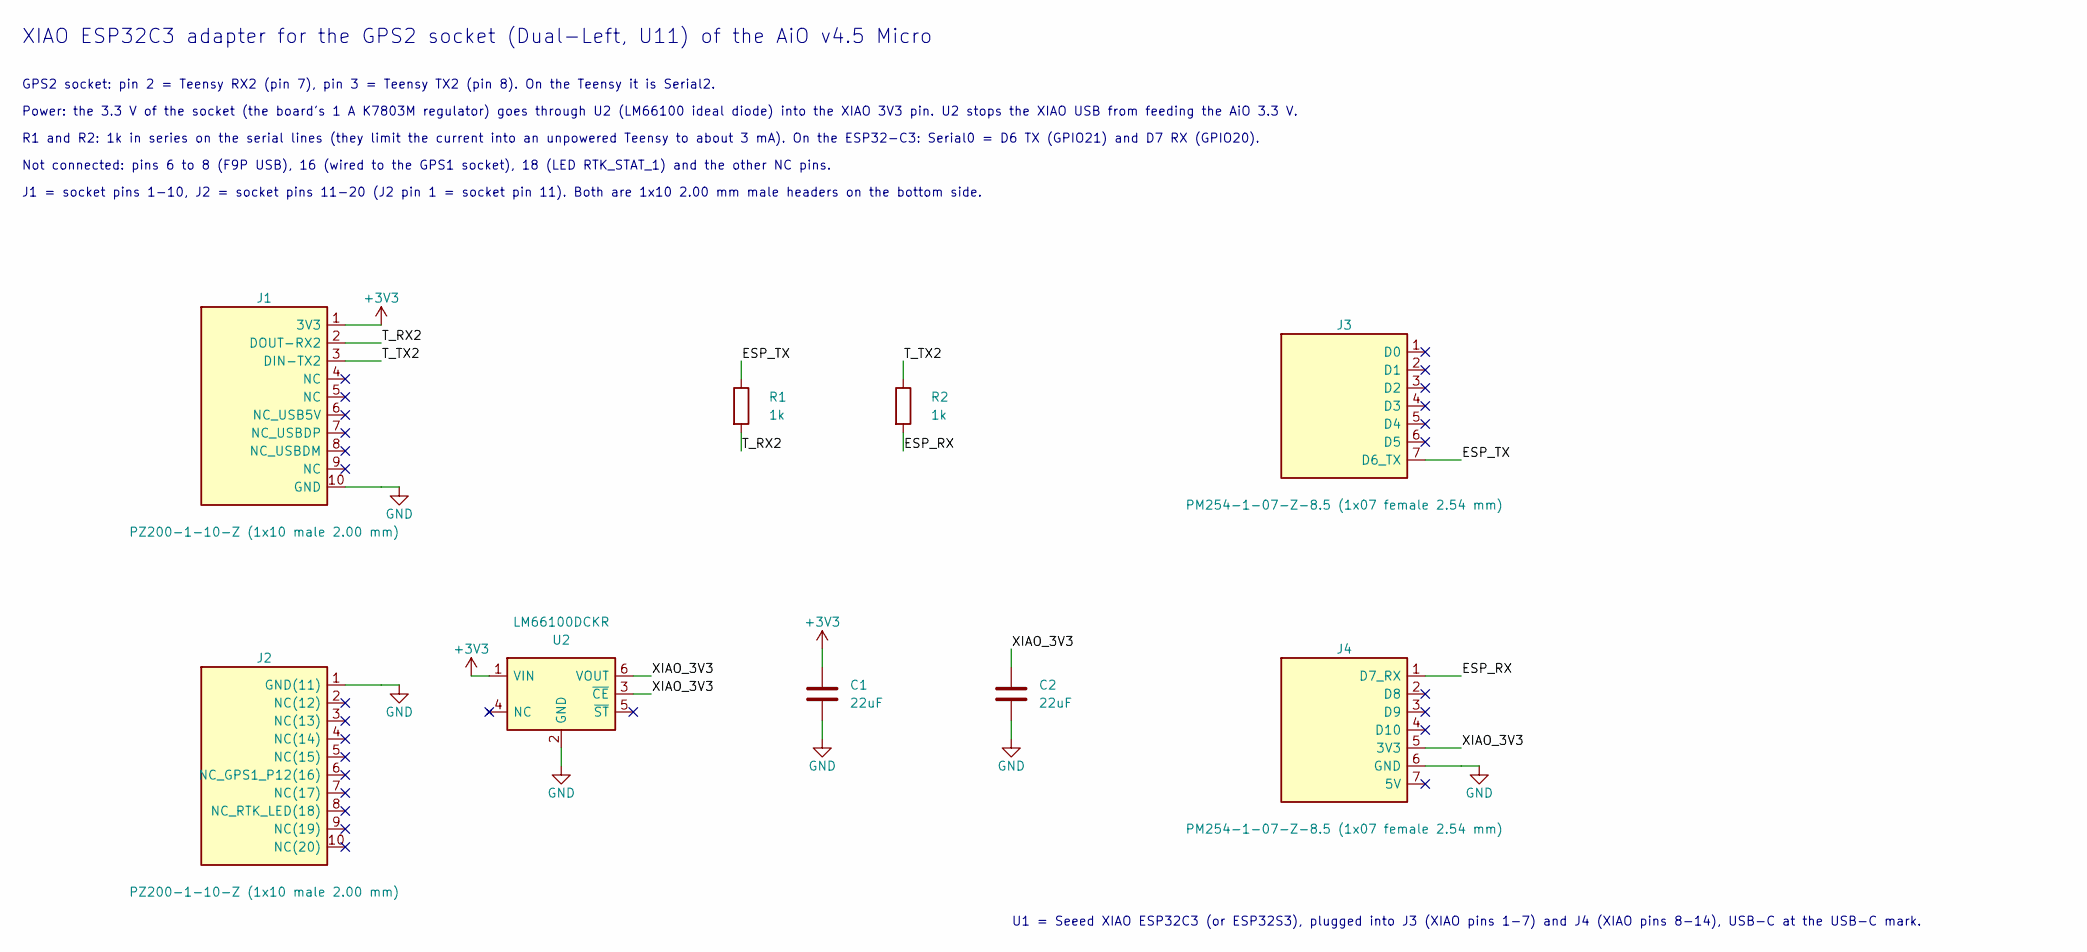
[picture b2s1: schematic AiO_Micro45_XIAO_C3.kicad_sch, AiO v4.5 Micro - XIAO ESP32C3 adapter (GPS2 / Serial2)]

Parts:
C1, C2: 22uF; C_0805_2012Metric; LCSC C45783
J1, J2: PZ200-1-10-Z (1x10 male 2.00 mm); Plug_1x10_P2.00mm_Bottom; LCSC C2905956
J3, J4: PM254-1-07-Z-8.5 (1x07 female 2.54 mm); Socket_1x07_P2.54mm_XIAO; LCSC C2897370
R1, R2: 1k; R_0805_2012Metric; LCSC C17513
U2: LM66100DCKR; SOT-363_SC-70-6; LCSC C2869734

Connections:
+3V3: C1.1, J1.1 (3V3), U2.1 (VIN)
/ESP_RX: J4.1 (D7_RX), R2.2
/ESP_TX: J3.7 (D6_TX), R1.1
/T_RX2: J1.2 (DOUT-RX2), R1.2
/T_TX2: J1.3 (DIN-TX2), R2.1
/XIAO_3V3: C2.1, J4.5 (3V3), U2.3 (~CE), U2.6 (VOUT)
GND: C1.2, C2.2, J1.10 (GND), J2.1 (GND(11)), J4.6 (GND), U2.2 (GND)

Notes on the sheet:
U1 = Seeed XIAO ESP32C3 (or ESP32S3), plugged into J3 (XIAO pins 1-7) and J4 (XIAO pins 8-14), USB-C at the USB-C mark.
XIAO ESP32C3 adapter for the GPS2 socket (Dual-Left, U11) of the AiO v4.5 Micro
GPS2 socket: pin 2 = Teensy RX2 (pin 7), pin 3 = Teensy TX2 (pin 8). On the Teensy it is Serial2.
Power: the 3.3 V of the socket (the board's 1 A K7803M regulator) goes through U2 (LM66100 ideal diode) into the XIAO 3V3 pin. U2 stops the XIAO USB from feeding the AiO 3.3 V.
R1 and R2: 1k in series on the serial lines (they limit the current into an unpowered Teensy to about 3 mA). On the ESP32-C3: Serial0 = D6 TX (GPIO21) and D7 RX (GPIO20).
Not connected: pins 6 to 8 (F9P USB), 16 (wired to the GPS1 socket), 18 (LED RTK_STAT_1) and the other NC pins.
J1 = socket pins 1-10, J2 = socket pins 11-20 (J2 pin 1 = socket pin 11). Both are 1x10 2.00 mm male headers on the bottom side.

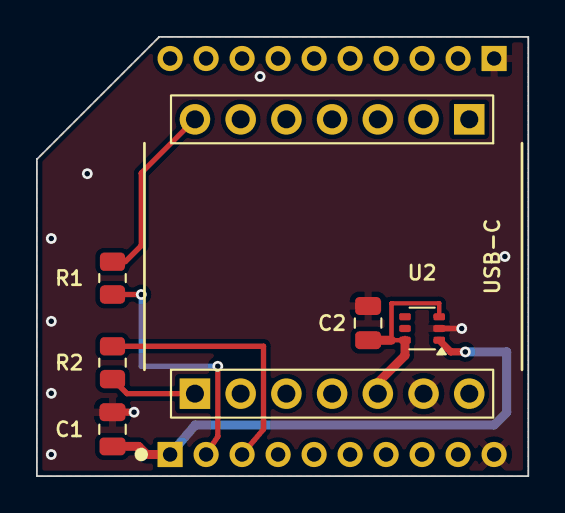
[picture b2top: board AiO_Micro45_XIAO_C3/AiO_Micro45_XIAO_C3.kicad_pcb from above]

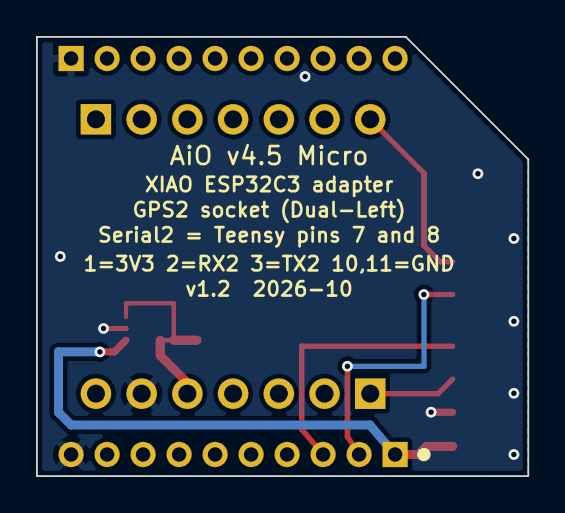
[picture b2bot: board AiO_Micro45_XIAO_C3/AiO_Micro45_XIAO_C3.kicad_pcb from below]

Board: 2 copper layers, 27.3 x 24.4 mm, 9 parts (2 on the bottom side), 7 nets.

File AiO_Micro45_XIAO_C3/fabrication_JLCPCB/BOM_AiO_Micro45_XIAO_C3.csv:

Comment,Designator,Footprint,LCSC Part #
1k 1% 0805,"R1,R2",R_0805_2012Metric,C17513
22uF 0805 X5R,"C1,C2",C_0805_2012Metric,C45783
LM66100DCKR ideal diode SC-70-6,U2,SOT-363_SC-70-6,C2869734
Pin header 1x10 male 2.00mm PZ200-1-10-Z (bottom side),"J1,J2",Plug_1x10_P2.00mm_Bottom,C2905956
Female header 1x07 2.54mm 8.5mm PM254-1-07-Z-8.5 (top side - XIAO socket),"J3,J4",Socket_1x07_P2.54mm_XIAO,C2897370
